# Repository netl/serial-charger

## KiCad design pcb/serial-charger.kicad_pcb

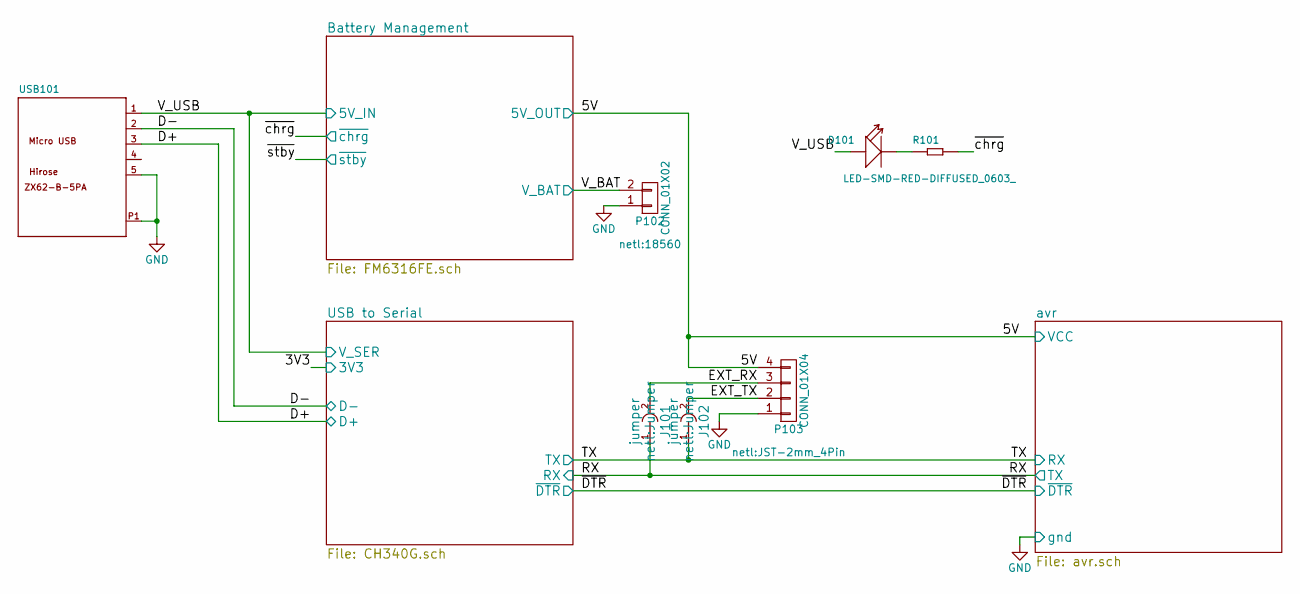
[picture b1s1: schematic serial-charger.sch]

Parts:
D101: LED-SMD-RED-DIFFUSED_0603_; LED-0603; MPN 19-217-R6C-AL1M2VY-3T
J101, J102: jumper; Jumper
P102: CONN_01X02; 18560
P103: CONN_01X04; JST-2mm_4Pin
R101: SMD-RES-1K-5%-1_10W_0603_; R0603; MPN RC0603JR-071KL
USB101: MICRO-USB-SMD_ZX62-B-5PA_; MICRO-USB5+4P-SMD-0.65-B; MPN ZX62-B-5PA

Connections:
/5V: P103.4; also elsewhere on the board
/D+: USB101.3 (D+); also elsewhere on the board
/D-: USB101.2 (D-); also elsewhere on the board
/EXT_RX: J101.2, P103.3
/EXT_TX: J102.2, P103.2
/RX: J101.1; also elsewhere on the board
/TX: J102.1; also elsewhere on the board
/V_BAT: P102.2; also elsewhere on the board
/V_USB: D101.+, USB101.1 (VBUS); also elsewhere on the board
/~chrg: R101.2; also elsewhere on the board
GND: P102.1, P103.1, USB101.5 (GND), USB101.P1 (SHIELD), USB101.P2 (SHIELD), USB101.P3 (SHIELD), USB101.P4 (SHIELD), USB101.P5 (SHIELD), USB101.P6 (SHIELD); also elsewhere on the board
unnamed: D101.-, R101.1

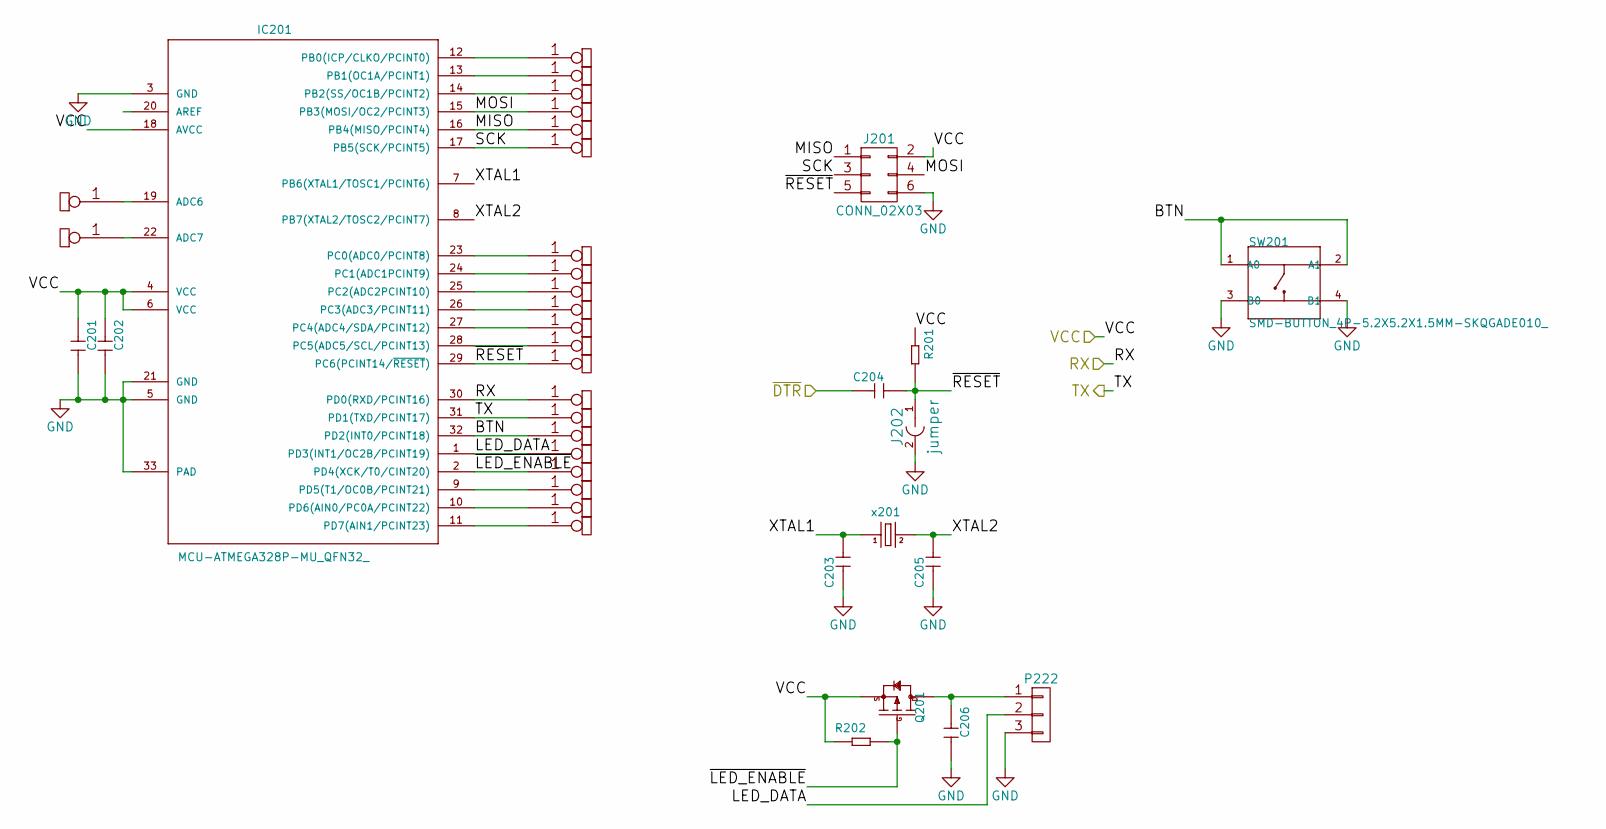
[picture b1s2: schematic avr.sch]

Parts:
C201, C202, C204: CERAMIC-100NF-50V-10%-X7R_0603_; C0603; MPN CC0603KRX7R9BB104
C203, C205: CERAMIC-22PF-50V-5%-NPO_0603_; C0603; MPN CC0603JRNPO9BN220
C206: CERAMIC-22UF-6.3V-20%-X5R_0805_; C0805; MPN CC0805MKX5R5BB226
IC201: MCU-ATMEGA328P-MU_QFN32_; QFN32G-0.5-5X5MM; MPN ATMEGA328P-MU
J201: CONN_02X03
J202: jumper
P201, P202, P203, P204, P205, P206, P207, P208, P209, P210, P211, P212, P213, P214, P215, P216, P217, P218, P219, P220, P221, P223, P224: CONNECTOR; 1Pin_small
P222: CONN_01X03; SM_3_WIRE
Q201: SMD-MOSFET-P-CH-8V-4.1A-CJ2305_SOT-23_; SOT-23; MPN CJ2305
R201, R202: SMD-RES-10K-1%-1_10W_0603_; R0603; MPN RC0603FR-0710KL
SW201: SMD-BUTTON_4P-5.2X5.2X1.5MM-SKQGADE010_; SW4-SMD-5.2X5.2X1.5MM; MPN SKQGADE010
x201: SMD-CRYSTAL-16MHZ-8PF-20PPM-40R_2P-5.0X3.2MM_; X2-SMD-5.0X3.2X1.3MM; MPN X053201602002

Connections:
/5V: C201.1, C202.1, IC201.4 (VCC), IC201.6 (VCC), IC201.18 (AVCC), J201.2, Q201.2 (S), R201.1, R202.1; also elsewhere on the board
/RX: IC201.31 (PD1(TXD/PCINT17)), P215.1; also elsewhere on the board
/TX: IC201.30 (PD0(RXD/PCINT16)), P214.1; also elsewhere on the board
/avr/BTN: IC201.32 (PD2(INT0/PCINT18)), P216.1, SW201.1 (A0), SW201.2 (A1)
/avr/LED_DATA: IC201.1 (PD3(INT1/OC2B/PCINT19)), P217.1, P222.2
/avr/MISO: IC201.16 (PB4(MISO/PCINT4)), J201.1, P205.1
/avr/MOSI: IC201.15 (PB3(MOSI/OC2/PCINT3)), J201.4, P204.1
/avr/SCK: IC201.17 (PB5(SCK/PCINT5)), J201.3, P206.1
/avr/XTAL1: C203.2, IC201.7 (PB6(XTAL1/TOSC1/PCINT6)), x201.1
/avr/XTAL2: C205.2, IC201.8 (PB7(XTAL2/TOSC2/PCINT7)), x201.2
/avr/~LED_ENABLE: IC201.2 (PD4(XCK/T0/CINT20)), P218.1, Q201.1 (G), R202.2
/avr/~RESET: C204.2, IC201.29 (PC6(PCINT14/~RESET)), J201.5, J202.1, P213.1, R201.2; also elsewhere on the board
/~DTR: C204.1; also elsewhere on the board
GND: C201.2, C202.2, C203.1, C205.1, C206.2, IC201.3 (GND), IC201.5 (GND), IC201.21 (GND), IC201.33 (PAD), J201.6, J202.2, P222.3, SW201.3 (B0), SW201.4 (B1); also elsewhere on the board
unnamed: C206.1, P222.1, Q201.3 (D)
unnamed: IC201.9 (PD5(T1/OC0B/PCINT21)), P219.1
unnamed: IC201.10 (PD6(AIN0/PC0A/PCINT22)), P220.1
unnamed: IC201.11 (PD7(AIN1/PCINT23)), P221.1
unnamed: IC201.12 (PB0(ICP/CLKO/PCINT0)), P201.1
unnamed: IC201.13 (PB1(OC1A/PCINT1)), P202.1
unnamed: IC201.14 (PB2(SS/OC1B/PCINT2)), P203.1
unnamed: IC201.19 (ADC6), P223.1
unnamed 37: IC201.20 (AREF); also elsewhere on the board
unnamed: IC201.22 (ADC7), P224.1
unnamed: IC201.23 (PC0(ADC0/PCINT8)), P207.1
unnamed: IC201.24 (PC1(ADC1PCINT9)), P208.1
unnamed: IC201.25 (PC2(ADC2PCINT10)), P209.1
unnamed: IC201.26 (PC3(ADC3/PCINT11)), P210.1
unnamed: IC201.27 (PC4(ADC4/SDA/PCINT12)), P211.1
unnamed: IC201.28 (PC5(ADC5/SCL/PCINT13)), P212.1

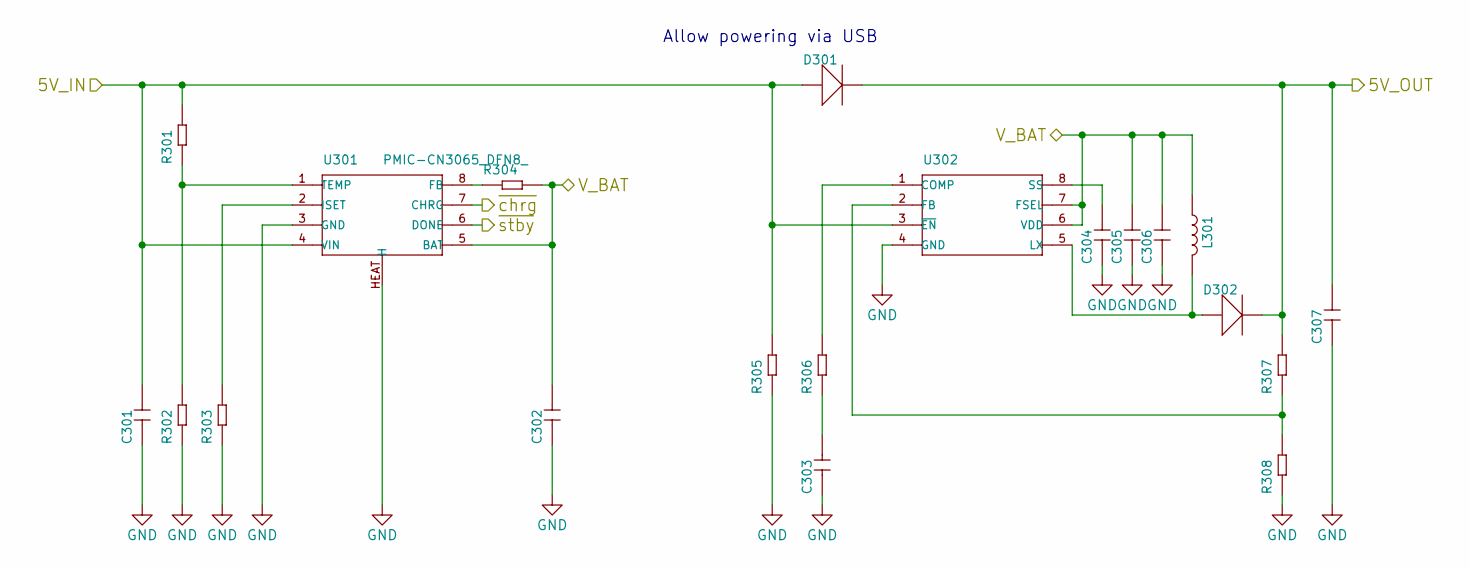
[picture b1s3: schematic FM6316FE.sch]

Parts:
C301, C302: CERAMIC-4.7UF-10V-10%-X5R_0603_; C0603; MPN CC0603KRX5R6BB475
C303: CERAMIC-4.7NF-50V-10%-X7R_0603_; C0603; MPN CC0603KRX7R9BB472
C304: CERAMIC-33NF-50V-10%-X7R_0603_; C0603; MPN CC0603KRX7R9BB333
C305: CERAMIC-100NF-50V-10%-X7R_0603_; C0603; MPN CC0603KRX7R9BB104
C306, C307: CERAMIC-22UF-6.3V-20%-X5R_0805_; C0805; MPN CC0805MKX5R5BB226
D301, D302: SMD-DIODE-SCHOTTKY-28V-5A_DO-214AA_; DO-214AA; MPN SS54B
L301: SMD-INDUCTOR-10UH-20%_2P-6X6MM_; SMD-2P-L6.0XW6.0XH3.0MM; MPN CSAB0630-100M
R301, R308: SMD-RES-10K-1%-1_10W_0603_; R0603; MPN RC0603FR-0710KL
R302: SMD-RES-0R-5%-1_10W_0603_; R0603; MPN RC0603JR-070RL
R303: SMD-RES-3.6R-5%-1_10W_0603_; R0603; MPN RC0603JR-073R6L
R304: SMD-RES-0R-5%-1_10W_0603_; R_0603; MPN RC0603JR-070RL
R305: SMD-RES-10K-5%-1_10W_0603_; R0603; MPN RC0603JR-0710KL
R306: SMD-RES-3.9K-5%-1_10W_0603_; R0603; MPN RC0603JR-073K9L
R307: SMD-RES-30K-1%-1_10W_0603_; R0603; MPN RC0603FR-0730KL
U301: PMIC-CN3065_DFN8_; DFN8G-0.5-3X3MM; MPN CN3065
U302: PMIC-ISL97516IUZ-TK_MSOP8_; MSOP8-0.65-3X3MM; MPN ISL97516IUZ-TK

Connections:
/5V: C307.2, D301.-, D302.-, R307.2; also elsewhere on the board
/V_BAT: C302.2, C305.2, C306.2, L301.1, R304.2, U301.5 (BAT), U302.6 (VDD), U302.7 (FSEL); also elsewhere on the board
/V_USB: C301.2, D301.+, R301.2, R305.2, U301.4 (VIN), U302.3 (~EN); also elsewhere on the board
/~chrg: U301.7 (CHRG); also elsewhere on the board
/~stby: U301.6 (DONE)
GND: C301.1, C302.1, C303.1, C304.1, C305.1, C306.1, C307.1, R302.1, R303.1, R305.1, R308.1, U301.3 (GND), U301.HEAT (H), U302.4 (GND); also elsewhere on the board
unnamed: C303.2, R306.1
unnamed: C304.2, U302.8 (SS)
unnamed: D302.+, L301.2, U302.5 (LX)
unnamed: R301.1, R302.2, U301.1 (TEMP)
unnamed: R303.2, U301.2 (ISET)
unnamed: R304.1, U301.8 (FB)
unnamed: R306.2, U302.1 (COMP)
unnamed: R307.1, R308.2, U302.2 (FB)

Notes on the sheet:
Allow powering via USB

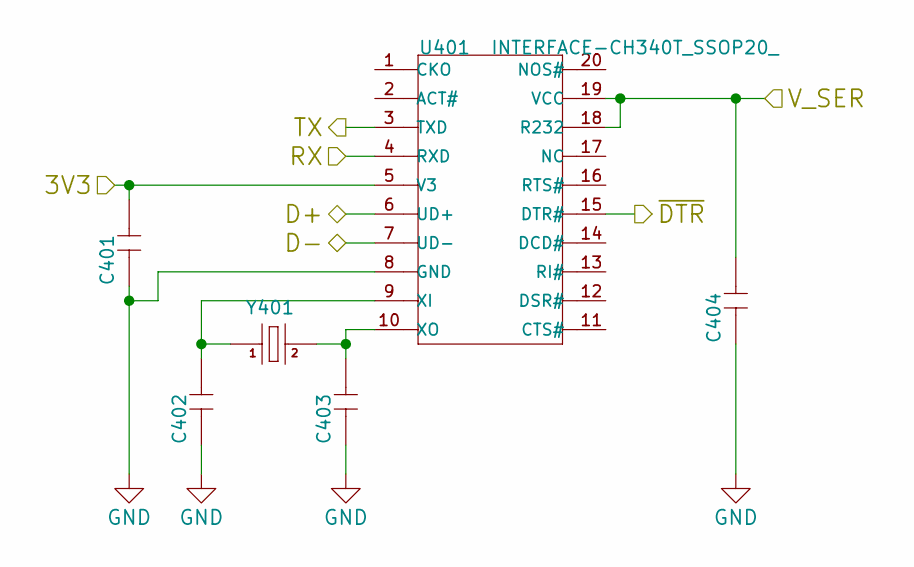
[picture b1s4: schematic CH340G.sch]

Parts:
C401, C404: CERAMIC-100NF-50V-10%-X7R_0603_; C0603; MPN CC0603KRX7R9BB104
C402, C403: CERAMIC-22PF-50V-5%-NPO_0603_; C0603; MPN CC0603JRNPO9BN220
U401: INTERFACE-CH340T_SSOP20_; TSSOP20-0.65-6.5X4.4MM; MPN CH340T
Y401: SMD-CRYSTAL-12MHZ-20PF-20PPM-40R_2P-5.0X3.2MM_; X2-SMD-5.0X3.2X1.3MM; MPN 5032_2P

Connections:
/3V3: C401.2, U401.5 (V3)
/D+: U401.6 (UD+); also elsewhere on the board
/D-: U401.7 (UD-); also elsewhere on the board
/RX: U401.4 (RXD); also elsewhere on the board
/TX: U401.3 (TXD); also elsewhere on the board
/V_USB: C404.2, U401.18 (R232), U401.19 (VCC); also elsewhere on the board
/~DTR: U401.15 (DTR#); also elsewhere on the board
GND: C401.1, C402.1, C403.1, C404.1, U401.8 (GND); also elsewhere on the board
unnamed: C402.2, U401.9 (XI), Y401.1
unnamed: C403.2, U401.10 (XO), Y401.2

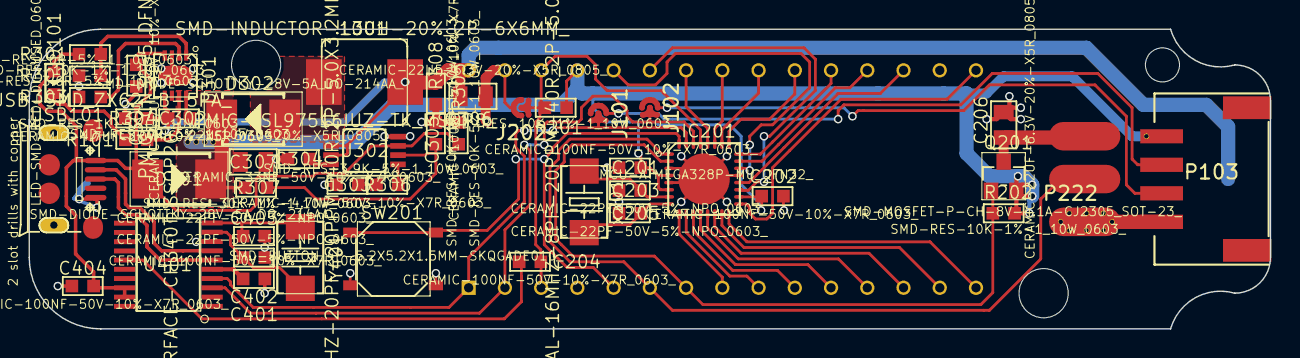
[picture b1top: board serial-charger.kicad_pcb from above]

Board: 2 copper layers, 87.0 x 21.0 mm, 77 parts (1 on the bottom side), 49 nets.

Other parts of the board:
JP11, JP11#2, JP11#3, JP11#4, JP11#5, JP11#6: CONN_01X01; 1Pin_through
P213#2: CONNECTOR; 1Pin_through

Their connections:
/5V: JP11#3.1; also elsewhere on the board
/V_BAT: JP11.1; also elsewhere on the board
/avr/~RESET: P213#2.1; also elsewhere on the board
GND: JP11#2.1, JP11#5.1; also elsewhere on the board
unnamed 37: JP11#4.1; also elsewhere on the board

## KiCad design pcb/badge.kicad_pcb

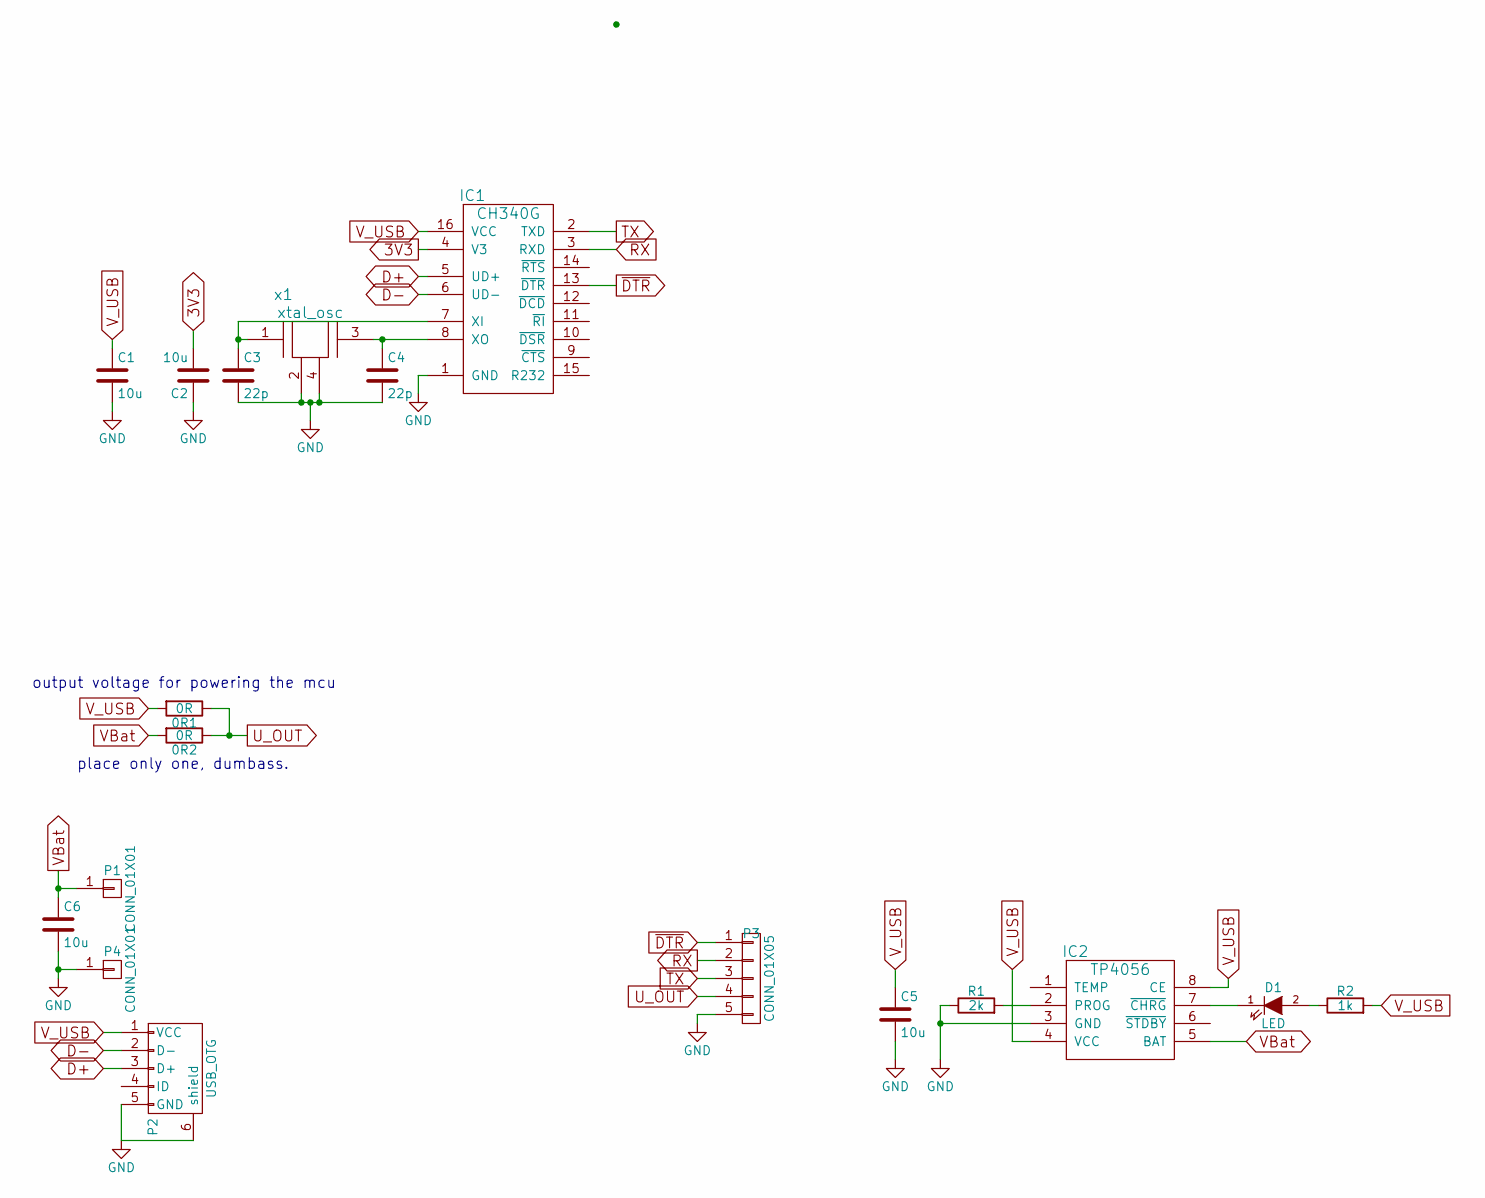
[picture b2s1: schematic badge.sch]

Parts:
0R1, 0R2: 0R; SMD_0603
C1, C2, C5, C6: 10u; SMD_0603
C3, C4: 22p; SMD_0603
D1: LED; SMD_0603
IC1: CH340G; SOIC-16_3.9x9.9mm_Pitch1.27mm
IC2: TP4056; SOIC-8-N
P1, P4: CONN_01X01; 1pin
P2: USB_OTG; USB_Micro-B
P3: CONN_01X05; Pin_Header_Angled_1x05
R1: 2k; SMD_0603
R2: 1k; SMD_0603
x1: xtal_osc; SM_3225

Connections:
3V3: C2.2, IC1.4 (V3)
D+: IC1.5 (UD+), P2.3 (D+)
D-: IC1.6 (UD-), P2.2 (D-)
GND: C1.2, C2.1, C3.2, C4.2, C5.2, C6.2, IC1.1 (GND), IC2.3 (GND), P2.5 (GND), P2.6 (shield), P3.5, P4.1, R1.1, x1.2, x1.4
unnamed: C3.1, IC1.7 (XI), x1.1
unnamed: C4.1, IC1.8 (XO), x1.3
unnamed: D1.1 (K), IC2.7 (~CHRG)
unnamed: D1.2 (A), R2.1
unnamed: IC2.2 (PROG), R1.2
RX: IC1.3 (RXD), P3.2
TX: IC1.2 (TXD), P3.3
U_OUT: 0R1.1, 0R2.1, P3.4
VBat: 0R2.2, C6.1, IC2.5 (BAT), P1.1
V_USB: 0R1.2, C1.1, C5.1, IC1.16 (VCC), IC2.4 (VCC), IC2.8 (CE), P2.1 (VCC), R2.2
~DTR: IC1.13 (~DTR), P3.1

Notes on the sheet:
place only one, dumbass.
output voltage for powering the mcu

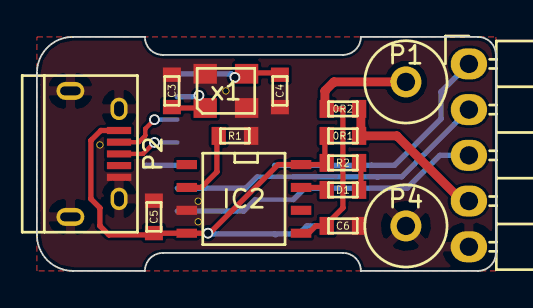
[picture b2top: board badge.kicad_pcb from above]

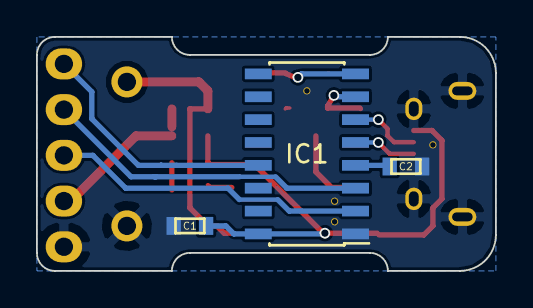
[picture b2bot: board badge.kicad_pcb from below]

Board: 2 copper layers, 25.5 x 13.0 mm, 18 parts (3 on the bottom side), 15 nets.

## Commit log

2016-09-01 started schema
2016-09-02 first complete version
2016-09-17 remved logic level shifter and updated component values
2016-10-08 updated layout to match schema
2016-10-16 removed 3V3 selection. cleaned up layout
2016-10-16 renamed project files
2016-10-16 cleanup, renamed output files to match kicad output
2016-10-16 disabled thermal shutoff from charger
2016-10-16 updated the other gerber files too. doh.
2017-02-28 changed regulator and jumpers
2017-03-02 changed charger
2017-03-04 partyhat edition, with built in avr and li-ion holder
2017-03-05 layout mostly done
2017-03-05 first prototype
2017-03-26 changed to hierarchial layout in schematics
2017-03-26 added documentation, moved gerber files to a separate directory
2017-04-04 changed LED and boost converters Diode footprints. renumbered components
2017-04-04 removed kicad backup file
2017-05-18 changed mcu to the correct one. redid layout
2017-06-14 updated component values
2017-06-14 fixed short circuits caused by oversized breakout pads
2017-06-14 centered battery tab connectors, reworked layout to match it
2017-06-18 cleaned up component values, rebuilt BOM
2017-06-18 added branding, updated documentation and gerber
2018-01-08 reworked bms and mcu to use seeed components
2018-01-09 added spi header for avr
2018-01-09 finished swapping parts, started layout
2018-01-10 added led strip power control, minor adjustments to layout
2018-01-27 boost circuit layout mostly done
2018-02-05 added button, capacitor to led strip power and jumpers to external rx/tx. everything layed out and connected
